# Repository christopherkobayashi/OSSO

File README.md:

# Osso

Osso is a BeagleBone (White/Black/Green) I/O expansion cape.

The Osso was designed by Franco (nextime) Lanza <franco@nexlab.it>

## Output

The Osso has 8 relays rated at 275VAC@10A.

## Input
Osso has 8 digital inputs.  They can be switched between opto-isolated and non-opto-isolated; the instructions are [here](INPUTS.md)

## Power

The expansion cape is powered by a 12VDC connector (9 to 24VDC supported).  The Osso will supply power to the BeagleBone via the expansion pins.

## Software

A test Debian GNU/Linux install is available.  Installation instructions are [here](TEST.md)

## Miscellaneous

The size of the cape is a standard format for 9 units DIN mount boxes.

## Pictures

Pin diagram (green dot pins are optional, other required):

## Miscellaneous

For more information, please visit https://www.nexlab.net/

Do you like our cape? Donations in Bitcoin is accepted at 1ABepVhyYuZNxiMQe8atPi4tRJZKkpRDqb (CK note: verify this address with nextime before sending any Bitcoin!)

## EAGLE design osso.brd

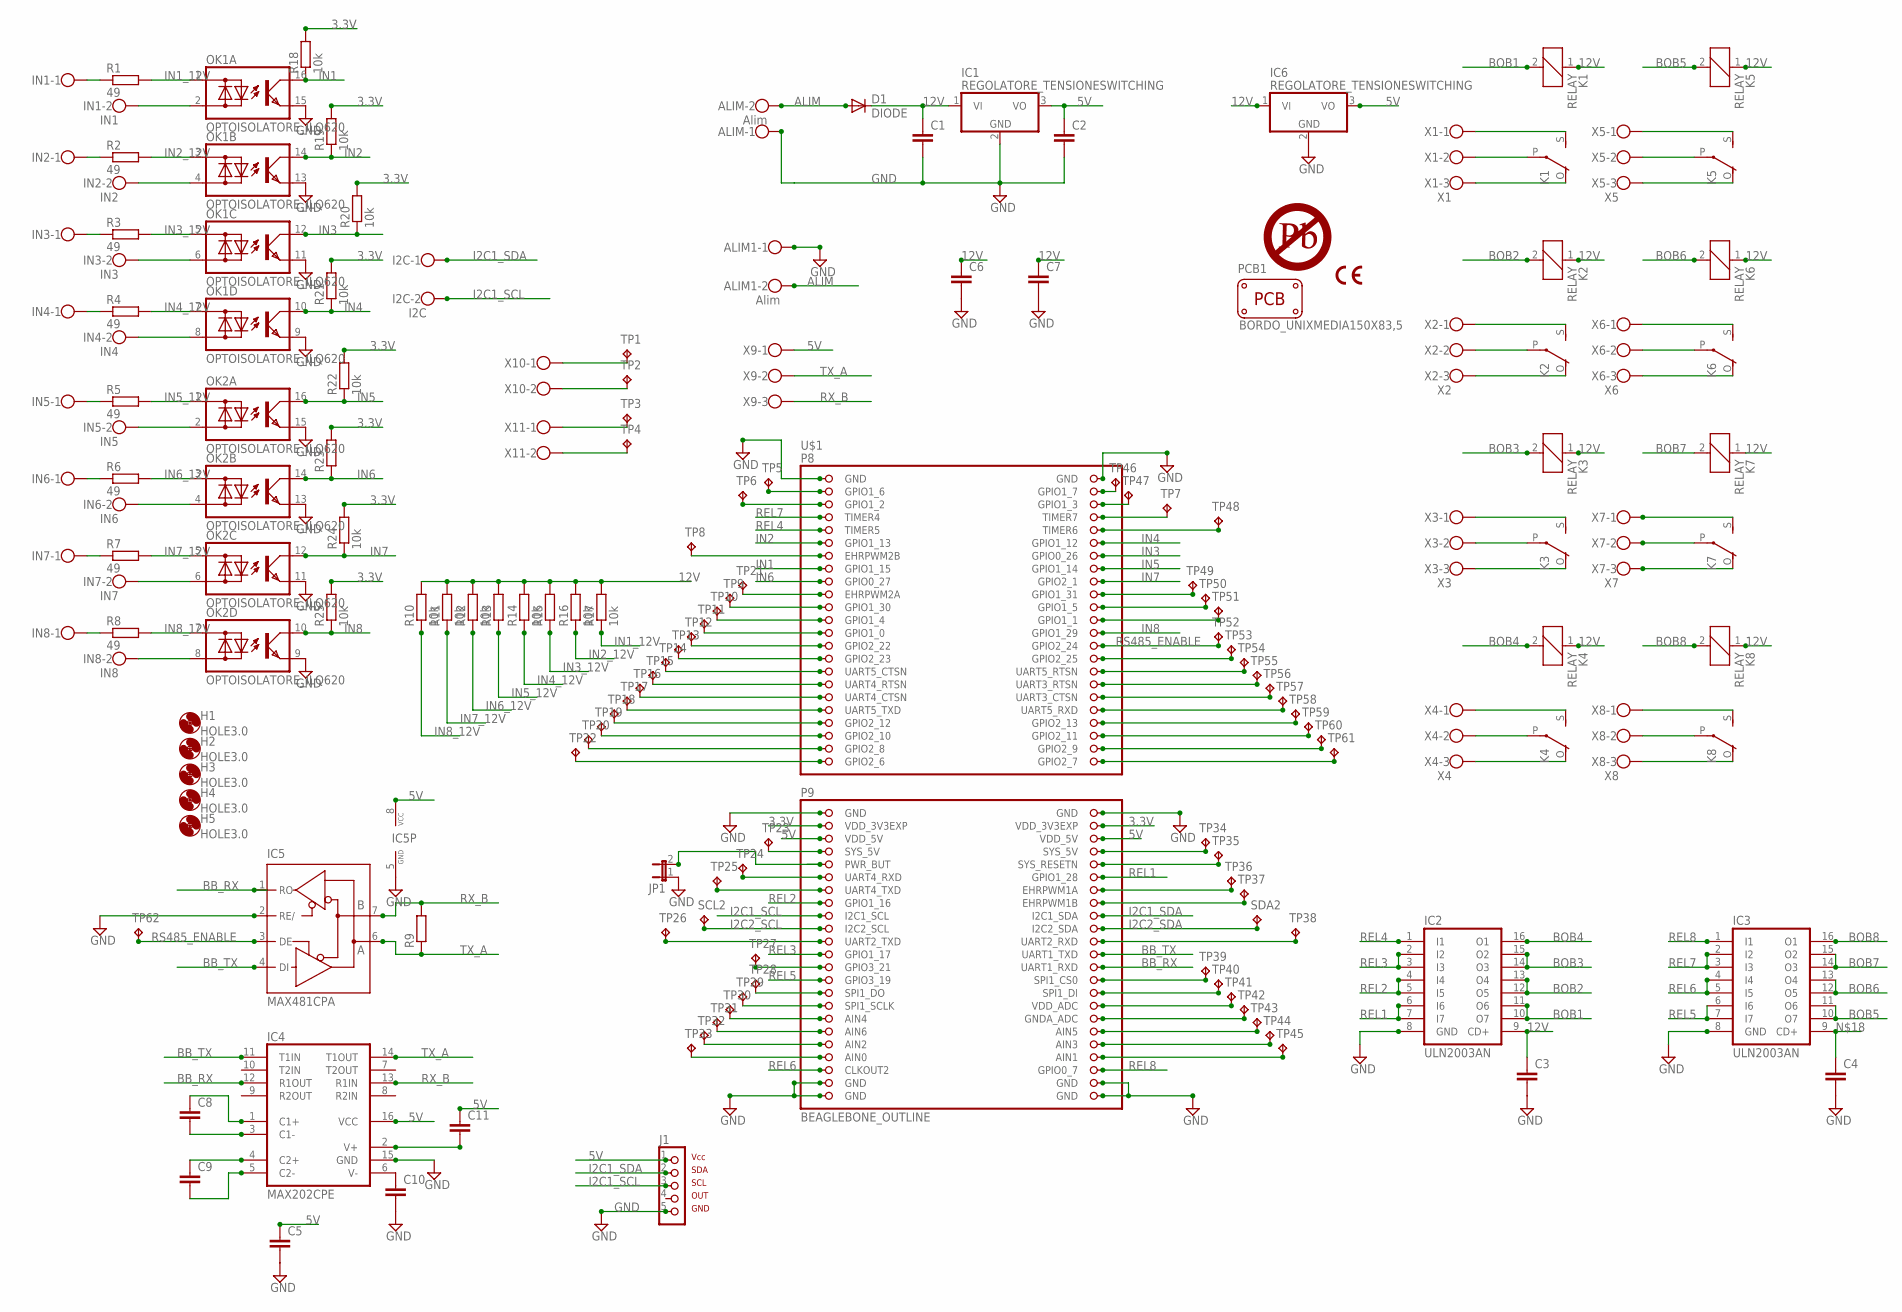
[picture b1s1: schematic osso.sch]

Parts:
ALIM: Alim; W237-102
ALIM1: Alim; W237-102; MPN 237-102
C1, C2, C3, C4, C5, C6, C7, C8, C9, C10, C11: C5/2.5; C5B2.5
D1: DIODE; DO15-12
H1, H2, H3, H4, H5: HOLE3.0; 3,0
I2C: I2C; W237-102; MPN 237-102
IC1, IC6: REGOLATORE_TENSIONESWITCHING; MT6-3
IC2, IC3: ULN2003AN; DIL16
IC4: MAX202CPE; DIL16
IC5: MAX481CPA; DIL08
IN1: IN1; W237-102
IN2: IN2; W237-102
IN3: IN3; W237-102
IN4: IN4; W237-102
IN5: IN5; W237-102
IN6: IN6; W237-102
IN7: IN7; W237-102
IN8: IN8; W237-102
J1: RTC_MICROROBOT_ALGOZINO-PTH; RTC_MICROBOT_ALGOZINO
JP1: JUMPER_2; JP1
K1, K2, K3, K4, K5, K6, K7, K8: RELAY; G5LE
OK1, OK2: OPTOISOLATORE_ILQ620; DIL16
PCB1: BORDO_UNIXMEDIA150X83,5; BORD_UNIXMEDIA
R1, R2, R3, R4, R5, R6, R7, R8: 49; 0204/7
R9, R13, R15, R23: RESISTOR0204/7; 0204/7
R10, R11, R12, R14, R16, R17, R18, R19, R20, R21, R22, R24, R25: 10k; 0204/7
SCL2: TPPAD1-13; TEST_POINT
SDA2: TP1; TEST_POINT
SS1: CE-MARK; CE-MARK-0.2
SS2: PB-MARK; PB-MARK-0.2
TP1, TP2, TP3, TP4, TP5, TP6, TP7, TP8, TP9, TP10, TP11, TP12, TP13, TP14, TP15, TP16, TP17, TP18, TP19, TP20, TP21, TP22, TP23, TP24, TP25, TP26, TP27, TP28, TP29, TP30, TP31, TP32, TP33, TP34, TP35, TP36, TP37, TP38, TP39, TP40, TP41, TP42, TP43, TP44, TP45, TP46, TP47, TP48, TP49, TP50, TP51, TP52, TP53, TP54, TP55, TP56, TP57, TP58, TP59, TP60, TP61, TP62: TPPAD1-13; TEST_POINT
U$1: BEAGLEBONE_OUTLINE; BEAGLEBONE_SHIELD
X1: X1; W237-103
X2: X2; W237-103
X3: X3; W237-103
X4: X4; W237-103
X5: X5; W237-103
X6: X6; W237-103
X7: X7; W237-103
X8: X8; W237-103
X9: MORSETTO_3; W237-103
X10, X11: MORSETTO_2; W237-102

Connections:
3.3V: R18.2, R19.2, R20.2, R21.2, R22.2, R23.2, R24.2, R25.2, U$1.49 (VDD_3V3EXP), U$1.50 (VDD_3V3EXP)
5V: C2.1, C5.1, C11.1, IC1.3 (VO), IC4.16 (VCC), IC5.8 (VCC), IC6.3 (VO), J1.1, U$1.51 (VDD_5V), U$1.52 (VDD_5V), X9.1
12V: C1.1, C3.1, C6.1, C7.1, D1.C, IC1.1 (VI), IC2.9 (CD+), IC6.1 (VI), K1.1, K2.1, K3.1, K4.1, K5.1, K6.1, K7.1, K8.1, R10.2, R11.2, R12.2, R13.2, R14.2, R15.2, R16.2, R17.2
ALIM: ALIM.2, ALIM1.2, D1.A
BB_RX: IC4.12 (R1OUT), IC5.1 (RO), U$1.72 (UART1_RXD)
BB_TX: IC4.11 (T1IN), IC5.4 (DI), U$1.70 (UART1_TXD)
BOB1: IC2.10 (O7), IC2.11 (O6), K1.2
BOB2: IC2.12 (O5), IC2.13 (O4), K2.2
BOB3: IC2.14 (O3), IC2.15 (O2), K3.2
BOB4: IC2.16 (O1), K4.2
BOB5: IC3.10 (O7), IC3.11 (O6), K5.2
BOB6: IC3.12 (O5), IC3.13 (O4), K6.2
BOB7: IC3.14 (O3), IC3.15 (O2), K7.2
BOB8: IC3.16 (O1), K8.2
GND: ALIM.1, ALIM1.1, C1.2, C2.2, C3.2, C4.2, C5.2, C6.2, C7.2, C10.2, IC1.2 (GND), IC2.8 (GND), IC3.8 (GND), IC4.15 (GND), IC5.2 (RE/), IC5.5 (GND), IC6.2 (GND), J1.5, JP1.1, OK1.9 (E), OK1.11 (E), OK1.13 (E), OK1.15 (E), OK2.9 (E), OK2.11 (E), OK2.13 (E), OK2.15 (E), U$1.1 (GND), U$1.2 (GND), U$1.47 (GND), U$1.48 (GND), U$1.89 (GND), U$1.90 (GND), U$1.91 (GND), U$1.92 (GND)
I2C1_SCL: I2C.2, J1.3, U$1.63 (I2C1_SCL)
I2C1_SDA: I2C.1, J1.2, U$1.64 (I2C1_SDA)
I2C2_SCL: SCL2.TP, U$1.65 (I2C2_SCL)
I2C2_SDA: SDA2.TP, U$1.66 (I2C2_SDA)
IN1: OK1.16 (C), R18.1, U$1.15 (GPIO1_15)
IN1_12V: OK1.1 (AC1), R1.2, R17.1
IN2: OK1.14 (C), R19.1, U$1.11 (GPIO1_13)
IN2_12V: OK1.3 (AC1), R2.2, R16.1
IN3: OK1.12 (C), R20.1, U$1.14 (GPIO0_26)
IN3_12V: OK1.5 (AC1), R3.2, R15.1
IN4: OK1.10 (C), R21.1, U$1.12 (GPIO1_12)
IN4_12V: OK1.7 (AC1), R4.2, R14.1
IN5: OK2.16 (C), R22.1, U$1.16 (GPIO1_14)
IN5_12V: OK2.1 (AC1), R5.2, R13.1
IN6: OK2.14 (C), R23.1, U$1.17 (GPIO0_27)
IN6_12V: OK2.3 (AC1), R6.2, R12.1
IN7: OK2.12 (C), R24.1, U$1.18 (GPIO2_1)
IN7_12V: OK2.5 (AC1), R7.2, R11.1
IN8: OK2.10 (C), R25.1, U$1.26 (GPIO1_29)
IN8_12V: OK2.7 (AC1), R8.2, R10.1
unnamed: IN1.1, R1.1
unnamed: TP1.TP, X10.1
unnamed: K5.S, X5.1
unnamed: K5.P, X5.2
unnamed: K5.O, X5.3
unnamed: K6.S, X6.1
unnamed: K6.P, X6.2
unnamed: K6.O, X6.3
unnamed: K3.S, X3.1
unnamed: K3.P, X3.2
unnamed: K3.O, X3.3
unnamed: C4.1, IC3.9 (CD+)
unnamed: K7.S, X7.1
unnamed: K7.P, X7.2
unnamed: K4.S, X4.1
unnamed: K4.P, X4.2
unnamed: K4.O, X4.3
unnamed: K8.S, X8.1
unnamed: K8.P, X8.2
unnamed: K8.O, X8.3
unnamed: IN2.1, R2.1
unnamed: TP2.TP, X10.2
unnamed: IN3.1, R3.1
unnamed: TP3.TP, X11.1
unnamed: IN4.1, R4.1
unnamed: TP4.TP, X11.2
unnamed: IN5.1, R5.1
unnamed: TP7.TP, U$1.8 (TIMER7)
unnamed: IN6.1, R6.1
unnamed: TP22.TP, U$1.45 (GPIO2_6)
unnamed: IN7.1, R7.1
unnamed: TP20.TP, U$1.43 (GPIO2_8)
unnamed: IN8.1, R8.1
unnamed: TP19.TP, U$1.41 (GPIO2_10)
unnamed: IN8.2, OK2.8 (AC2)
unnamed: IN7.2, OK2.6 (AC2)
unnamed: IN6.2, OK2.4 (AC2)
unnamed: IN5.2, OK2.2 (AC2)
unnamed: IN1.2, OK1.2 (AC2)
unnamed: IN2.2, OK1.4 (AC2)
unnamed: IN3.2, OK1.6 (AC2)
unnamed: IN4.2, OK1.8 (AC2)
unnamed: JP1.2, U$1.55 (PWR_BUT)
unnamed: TP18.TP, U$1.39 (GPIO2_12)
unnamed: TP17.TP, U$1.37 (UART5_TXD)
unnamed: TP16.TP, U$1.35 (UART4_CTSN)
unnamed: TP15.TP, U$1.33 (UART4_RTSN)
unnamed: TP14.TP, U$1.31 (UART5_CTSN)
unnamed: TP13.TP, U$1.29 (GPIO2_23)
unnamed: TP12.TP, U$1.27 (GPIO2_22)
unnamed: TP11.TP, U$1.25 (GPIO1_0)
unnamed: TP10.TP, U$1.23 (GPIO1_4)
unnamed: TP9.TP, U$1.21 (GPIO1_30)
unnamed: TP21.TP, U$1.19 (EHRPWM2A)
unnamed: TP5.TP, U$1.3 (GPIO1_6)
unnamed: TP6.TP, U$1.5 (GPIO1_2)
unnamed: K7.O, X7.3
unnamed: TP8.TP, U$1.13 (EHRPWM2B)
unnamed: TP33.TP, U$1.85 (AIN0)
unnamed: TP32.TP, U$1.83 (AIN2)
unnamed: TP31.TP, U$1.81 (AIN6)
unnamed: TP30.TP, U$1.79 (AIN4)
unnamed: TP29.TP, U$1.77 (SPI1_SCLK)
unnamed: TP28.TP, U$1.75 (SPI1_DO)
unnamed: TP27.TP, U$1.71 (GPIO3_21)
unnamed: TP26.TP, U$1.67 (UART2_TXD)
unnamed: TP25.TP, U$1.59 (UART4_TXD)
unnamed: TP24.TP, U$1.57 (UART4_RXD)
unnamed: TP23.TP, U$1.53 (SYS_5V)
unnamed: TP34.TP, U$1.54 (SYS_5V)
unnamed: TP35.TP, U$1.56 (SYS_RESETN)
unnamed: TP36.TP, U$1.60 (EHRPWM1A)
unnamed: TP37.TP, U$1.62 (EHRPWM1B)
unnamed: TP38.TP, U$1.68 (UART2_RXD)
unnamed: TP39.TP, U$1.74 (SPI1_CS0)
unnamed: TP40.TP, U$1.76 (SPI1_DI)
unnamed: TP41.TP, U$1.78 (VDD_ADC)
unnamed: TP42.TP, U$1.80 (GNDA_ADC)
unnamed: TP43.TP, U$1.82 (AIN5)
unnamed: TP44.TP, U$1.84 (AIN3)
unnamed: TP45.TP, U$1.86 (AIN1)
unnamed: TP61.TP, U$1.46 (GPIO2_7)
unnamed: TP60.TP, U$1.44 (GPIO2_9)
unnamed: TP59.TP, U$1.42 (GPIO2_11)
unnamed: TP58.TP, U$1.40 (GPIO2_13)
unnamed: TP57.TP, U$1.38 (UART5_RXD)
unnamed: TP56.TP, U$1.36 (UART3_CTSN)
unnamed: TP55.TP, U$1.34 (UART3_RTSN)
unnamed: TP54.TP, U$1.32 (UART5_RTSN)
unnamed: TP53.TP, U$1.30 (GPIO2_25)
unnamed: TP51.TP, U$1.24 (GPIO1_1)
unnamed: TP50.TP, U$1.22 (GPIO1_5)
unnamed: TP49.TP, U$1.20 (GPIO1_31)
unnamed: TP48.TP, U$1.10 (TIMER6)
unnamed: TP47.TP, U$1.6 (GPIO1_3)
unnamed: TP46.TP, U$1.4 (GPIO1_7)
unnamed: C8.1, IC4.1 (C1+)
unnamed: C8.2, IC4.3 (C1-)
unnamed: C9.1, IC4.4 (C2+)
unnamed: C9.2, IC4.5 (C2-)
R1_C: K1.P, X1.2
R1_NA: K1.S, X1.1
R1_NC: K1.O, X1.3
R2_C: K2.P, X2.2
R2_NA: K2.S, X2.1
R2_NC: K2.O, X2.3
REL1: IC2.6 (I6), IC2.7 (I7), U$1.58 (GPIO1_28)
REL2: IC2.4 (I4), IC2.5 (I5), U$1.61 (GPIO1_16)
REL3: IC2.2 (I2), IC2.3 (I3), U$1.69 (GPIO1_17)
REL4: IC2.1 (I1), U$1.9 (TIMER5)
REL5: IC3.6 (I6), IC3.7 (I7), U$1.73 (GPIO3_19)
REL6: IC3.4 (I4), IC3.5 (I5), U$1.87 (CLKOUT2)
REL7: IC3.2 (I2), IC3.3 (I3), U$1.7 (TIMER4)
REL8: IC3.1 (I1), U$1.88 (GPIO0_7)
RS485_ENABLE: IC5.3 (DE), TP52.TP, TP62.TP, U$1.28 (GPIO2_24)
RX_B: IC4.13 (R1IN), IC5.7 (B), R9.2, X9.3
TX_A: IC4.14 (T1OUT), IC5.6 (A), R9.1, X9.2
V+: C11.2, IC4.2 (V+)
V-: C10.1, IC4.6 (V-)

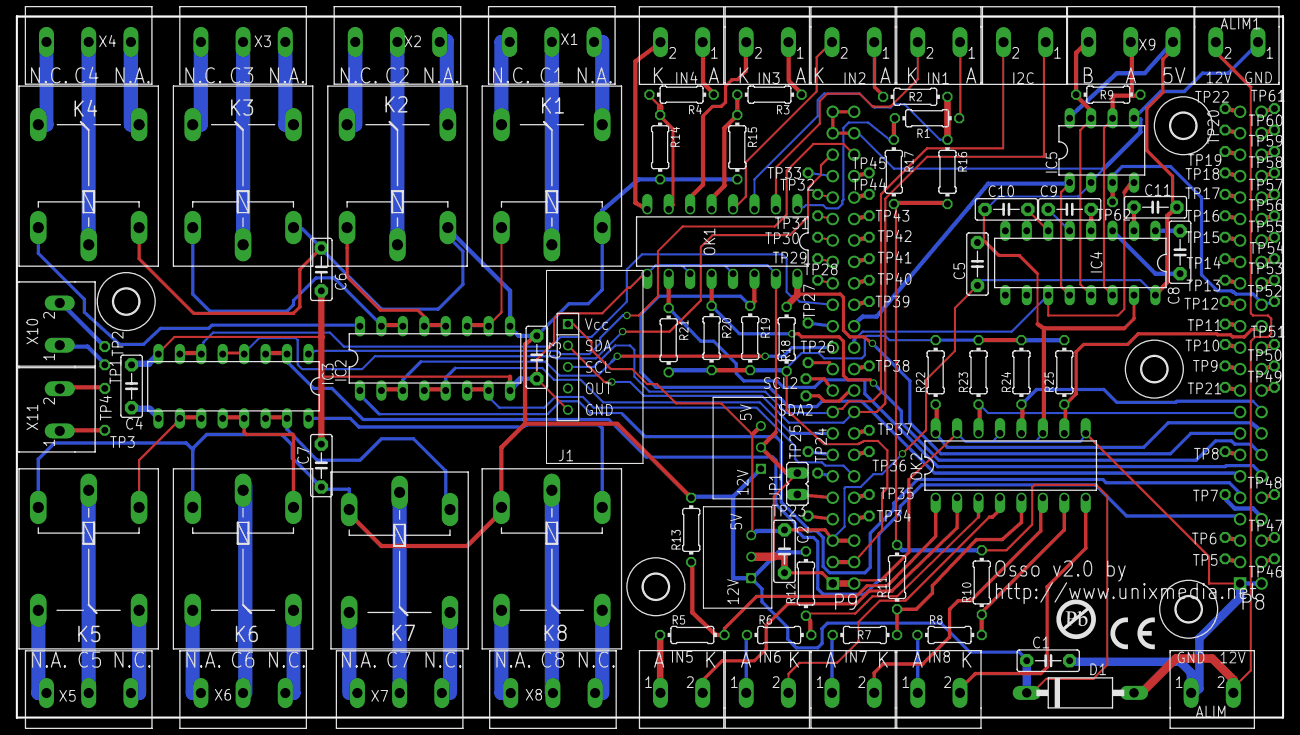
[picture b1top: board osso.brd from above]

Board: 4 copper layers, 150.0 x 83.1 mm, 150 parts (1 on the bottom side), 154 nets.

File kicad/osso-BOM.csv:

"Source:","/home/wileyc/src/OSSO/kicad/osso.kicad_sch"
"Date:","Fri 27 Jan 2023 08:09:53 PM JST"
"Tool:","Eeschema (6.0.11)"
"Generator:","/usr/share/kicad/plugins/bom_csv_grouped_by_value_with_fp.py"
"Component Count:","150"
"Ref","Qnty","Value","Cmp name","Footprint","Description","Vendor"
"ALIM0, ALIM1, ","2","Alim","MORSETTO_2","osso:W237-102","",""
"C1, C2, C3, C4, C5, C6, C7, C8, C9, C10, C11, ","11","C5/2.5","C5{slash}2.5","osso:C5B2.5","",""
"D1, ","1","DIODE","DIODE","osso:DO15-12","",""
"H1, H2, H3, H4, H5, ","5","HOLE3.0","HOLE3.0","osso:3,0","",""
"I2C0, ","1","I2C","MORSETTO_2","osso:W237-102","",""
"IC1, IC6, ","2","REGOLATORE_TENSIONESWITCHING","REGOLATORE_TENSIONESWITCHING","osso:MT6-3","",""
"IC2, IC3, ","2","ULN2003AN","ULN2003AN","osso:DIL16","",""
"IC4, ","1","MAX202CPE","MAX202CPE","osso:DIL16","",""
"IC5, ","1","MAX481CPA","MAX481CPA","osso:DIL08","",""
"IN1, ","1","IN1","MORSETTO_2","osso:W237-102","",""
"IN2, ","1","IN2","MORSETTO_2","osso:W237-102","",""
"IN3, ","1","IN3","MORSETTO_2","osso:W237-102","",""
"IN4, ","1","IN4","MORSETTO_2","osso:W237-102","",""
"IN5, ","1","IN5","MORSETTO_2","osso:W237-102","",""
"IN6, ","1","IN6","MORSETTO_2","osso:W237-102","",""
"IN7, ","1","IN7","MORSETTO_2","osso:W237-102","",""
"IN8, ","1","IN8","MORSETTO_2","osso:W237-102","",""
"J1, ","1","RTC_MICROROBOT_ALGOZINO-PTH","RTC_MICROROBOT_ALGOZINO-PTH","osso:RTC_MICROBOT_ALGOZINO","",""
"JP1, ","1","JUMPER_2","JUMPER_2","osso:JP1","",""
"K1, K2, K3, K4, K5, K6, K7, K8, ","8","RELAY","RELAY","osso:G5LE","",""
"OK1, OK2, ","2","OPTOISOLATORE_ILQ620","OPTOISOLATORE_ILQ620","osso:DIL16","",""
"PCB1, ","1","BORDO_UNIXMEDIA150X83,5","BORDO_UNIXMEDIA150X83,5","osso:BORD_UNIXMEDIA","",""
"R1, R2, R3, R4, R5, R6, R7, R8, ","8","49","RESISTOR0204{slash}7","osso:0204_7","",""
"R9, R13, R15, R23, ","4","RESISTOR0204/7","RESISTOR0204{slash}7","osso:0204_7","",""
"R10, R11, R12, R14, R16, R17, R18, R19, R20, R21, R22, R24, R25, ","13","10k","RESISTOR0204{slash}7","osso:0204_7","",""
"SCL2, ","1","TPPAD1-13","TPPAD1-13","osso:TEST_POINT","",""
"SDA2, ","1","TP1","TPPAD1-13","osso:TEST_POINT","",""
"SS1, ","1","CE-MARK","CE-MARK","osso:CE-MARK-0.2","",""
"SS2, ","1","PB-MARK","PB-MARK","osso:PB-MARK-0.2","",""
"TP1, TP2, TP3, TP4, TP5, TP6, TP7, TP8, TP9, TP10, TP11, TP12, TP13, TP14, TP15, TP16, TP17, TP18, TP19, TP20, TP21, TP22, TP23, TP24, TP25, TP26, TP27, TP28, TP29, TP30, TP31, TP32, TP33, TP34, TP35, TP36, TP37, TP38, TP39, TP40, TP41, TP42, TP43, TP44, TP45, TP46, TP47, TP48, TP49, TP50, TP51, TP52, TP53, TP54, TP55, TP56, TP57, TP58, TP59, TP60, TP61, TP62, ","62","TPPAD1-13","TPPAD1-13","osso:TEST_POINT","",""
"U$1, ","1","BEAGLEBONE_OUTLINE","BEAGLEBONE_OUTLINE","osso:BEAGLEBONE_SHIELD","",""
"X1, ","1","X1","MORSETTO_3","osso:W237-103","",""
"X2, ","1","X2","MORSETTO_3","osso:W237-103","",""
"X3, ","1","X3","MORSETTO_3","osso:W237-103","",""
"X4, ","1","X4","MORSETTO_3","osso:W237-103","",""
"X5, ","1","X5","MORSETTO_3","osso:W237-103","",""
"X6, ","1","X6","MORSETTO_3","osso:W237-103","",""
"X7, ","1","X7","MORSETTO_3","osso:W237-103","",""
"X8, ","1","X8","MORSETTO_3","osso:W237-103","",""
"X9, ","1","MORSETTO_3","MORSETTO_3","osso:W237-103","",""
"X10, X11, ","2","MORSETTO_2","MORSETTO_2","osso:W237-102","",""

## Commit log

2022-12-30 Initial import.
2022-12-30 Add KiCAD conversion.
2022-12-30 Move Eagle files to subdirectory.
2022-12-30 Remove zero-byte file.
2022-12-30 Move docs to doc/
2022-12-30 Add gerbers.
2023-01-27 Clean up docs a bit.
2023-01-27 Add test image instructions.
2023-01-27 Fix link.
2023-01-27 Add BOM and footprints.
2023-01-27 Rework documentation a bit more.
2023-01-27 *sigh* Whitespace.
2023-01-27 More typos.
2023-01-27 One more.
